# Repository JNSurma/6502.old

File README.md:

# 6502_sbc
My 6502 SBC Based on Ben Eater's 6502 Breadboard Computer

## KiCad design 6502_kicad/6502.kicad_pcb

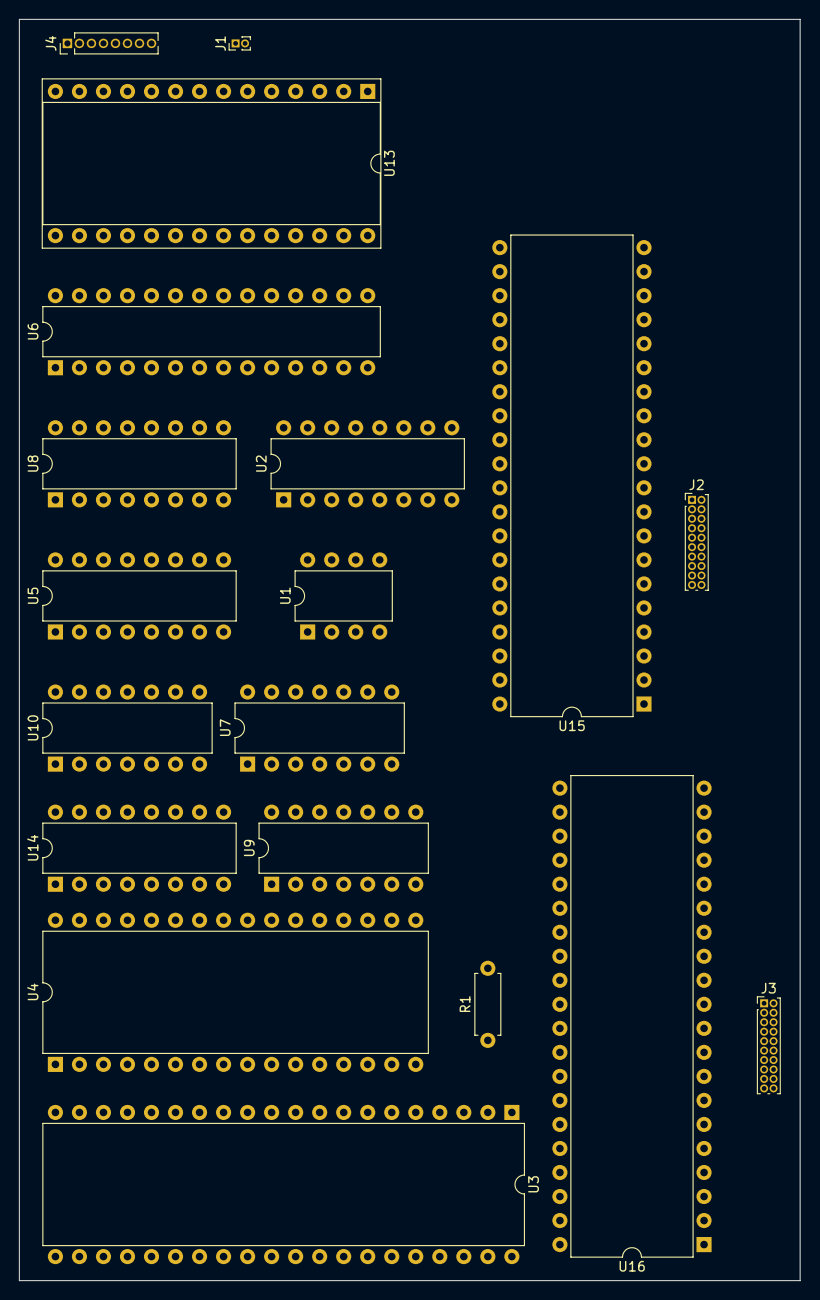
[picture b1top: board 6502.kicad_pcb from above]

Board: 2 copper layers, 82.5 x 133.4 mm, 19 parts (0 on the bottom side), 100 nets, no tracks yet.

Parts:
J1: Conn_01x02; PinHeader_1x02_P1.00mm_Vertical
J2, J3: Conn_02x10_Odd_Even; PinHeader_2x10_P1.00mm_Vertical
J4: Conn_01x08; PinHeader_1x08_P1.27mm_Vertical
R1: 1K; R_Axial_DIN0207_L6.3mm_D2.5mm_P7.62mm_Horizontal
U1: 24LC256; DIP-8_W7.62mm
U2, U5, U8: 74HC595; DIP-16_W7.62mm
U3: WD65C02; DIP-40_W15.24mm
U4: 628128; DIP-32_W15.24mm
U6: ATmega328P-PU; DIP-28_W7.62mm
U7: 74LS30; DIP-14_W7.62mm
U9: 74LS08; DIP-14_W7.62mm
U10: 74HC04; DIP-14_W7.62mm
U13: W65C51N; DIP-28_W15.24mm_Socket
U14: 74LS138; DIP-16_W7.62mm
U15, U16: WD65C22; DIP-40_W15.24mm

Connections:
+5V: R1.2, U3.8, U13.15, U14.16, U15.20, U16.20
/a0: U3.9, U4.12, U5.7, U14.1, U15.38, U16.38
/a1: U3.10, U4.11, U5.6, U14.2, U15.37, U16.37
/a2: U3.11, U4.10, U5.5, U14.3, U15.36, U16.36
/a3: U3.12, U4.9, U5.4, U15.35, U16.35
/a4: U3.13, U4.8, U5.3
/a5: U3.14, U4.7, U5.2
/a6: U3.15, U4.6, U5.1
/a7: U3.16, U4.5, U5.15, U10.3
/a8: U3.17, U4.27, U7.12, U8.7
/a9: U3.18, U4.26, U7.11, U8.6
/a10: U3.19, U4.23, U7.6, U8.5
/a11: U3.20, U4.25, U7.5, U8.4
/a12: U3.22, U4.4, U7.4, U8.3
/a13: U3.23, U4.28, U7.3, U8.2
/a14: U3.24, U4.3, U7.2, U8.1
/a15: U3.25, U4.31, U7.1, U8.15
/d0: U2.7, U3.33, U4.13, U6.14, U13.18, U15.33, U16.33
/d1: U2.6, U3.32, U4.14, U6.15, U13.19, U15.32, U16.32
/d2: U2.5, U3.31, U4.15, U6.4, U13.20, U15.31, U16.31
/d3: U2.4, U3.30, U4.17, U6.5, U13.21, U15.30, U16.30
/d4: U2.3, U3.29, U4.18, U6.6, U13.22, U15.29, U16.29
/d5: U2.2, U3.28, U4.19, U6.11, U13.23, U15.28, U16.28
/d6: U2.1, U3.27, U4.20, U6.12, U13.24, U15.27, U16.27
/d7: U2.15, U3.26, U4.21, U6.13, U13.25, U15.26, U16.26
GND: U3.21, U4.16, U4.22, U13.1, U14.5, U14.6, U14.8, U15.1, U16.1
unnamed: J1.1, U13.7
unnamed: J1.2, U13.6
unnamed: J2.1, U15.18
unnamed: J2.2, U15.19
unnamed: J2.3, U15.16
unnamed: J2.4, U15.15
unnamed: J2.5, U15.14
unnamed: J2.6, U15.13
unnamed: J2.7, U15.12
unnamed: J2.8, U15.17
unnamed: J2.9, U15.10
unnamed: J2.10, U15.11
unnamed: J2.11, U15.8
unnamed: J2.12, U15.9
unnamed: J2.13, U15.6
unnamed: J2.14, U15.7
unnamed: J2.15, U15.4
unnamed: J2.16, U15.5
unnamed: J2.17, U15.2
unnamed: J2.18, U15.3
unnamed: J2.19, U15.40
unnamed: J2.20, U15.39
unnamed: J3.1, U16.18
unnamed: J3.2, U16.19
unnamed: J3.3, U16.16
unnamed: J3.4, U16.15
unnamed: J3.5, U16.14
unnamed: J3.6, U16.13
unnamed: J3.7, U16.12
unnamed: J3.8, U16.17
unnamed: J3.9, U16.10
unnamed: J3.10, U16.11
unnamed: J3.11, U16.8
unnamed: J3.12, U16.9
unnamed: J3.13, U16.6
unnamed: J3.14, U16.7
unnamed: J3.15, U16.4
unnamed: J3.16, U16.5
unnamed: J3.17, U16.2
unnamed: J3.18, U16.3
unnamed: J3.19, U16.40
unnamed: J3.20, U16.39
unnamed: J4.1, U13.17
unnamed: J4.2, U13.16
unnamed: J4.3, U13.12
unnamed: J4.4, U13.11
unnamed: J4.5, U13.10
unnamed: J4.6, U13.9
unnamed: J4.7, U13.8
unnamed: J4.8, U13.5
unnamed: R1.1, U3.2
unnamed: U1.1, U1.2, U1.3, U2.8, U5.8
unnamed: U1.5, U6.27
unnamed: U1.6, U6.28
unnamed: U2.10, U2.12, U2.16, U5.10, U5.12, U5.16, U8.10, U8.12
unnamed: U2.11, U5.11, U6.18, U8.11
unnamed: U2.13, U5.13, U6.19, U8.13
unnamed: U2.14, U5.9
unnamed: U4.30, U9.6
unnamed: U5.14, U8.9
unnamed: U6.8, U6.22
unnamed: U6.26, U8.14
unnamed: U7.8, U10.1
unnamed: U9.2, U10.2
unnamed: U9.1, U10.4
unnamed: U4.24, U9.3, U10.5, U14.4, U15.24, U16.24
unnamed: U9.4, U10.6
unnamed: U14.14, U15.23
unnamed: U14.15, U16.23
unnamed: U3.4, U15.21, U16.21
unnamed: U3.34, U4.29, U15.22, U16.22
unnamed: U3.37, U9.5, U15.25, U16.25
unnamed: U3.40, U6.17, U15.34, U16.34
VCC: U3.36, U4.32

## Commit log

2020-07-18 Initial Commit.
2020-07-19 Added Serial EEPROM to RAM Arduino Project.
2020-07-20 Change permissions on a few files.
2020-07-21 Rotated 6522's to proper orientation.
2020-07-23 Add debug symbols. Untested.
2020-07-24 Working on kicad.
2020-07-26 Turned cursor off in hello world Ben Eater's 6502 program.
2020-08-15 Last commit before changing to ROM/RAM configuration.
2020-10-18 Start working on interrupt section of Ben's videos.
2020-10-18 Print 42 by cheating.
2020-10-18 Binary to decimal can’t be that hard, right?
2020-10-18 Rename irq.s to b2d.s (Binary to Decimal). New broken irq.s file
2020-10-18 BiHardware Interrupts
2020-10-18 Interrupt Handling
2020-11-02 Tidy up code and add images for SEEPROM 2 RAM circut. Abandoned, too slow.
2020-11-02 Add image files to serial_eeprom_2_ram of circut. Abandoned due to slow execution.
